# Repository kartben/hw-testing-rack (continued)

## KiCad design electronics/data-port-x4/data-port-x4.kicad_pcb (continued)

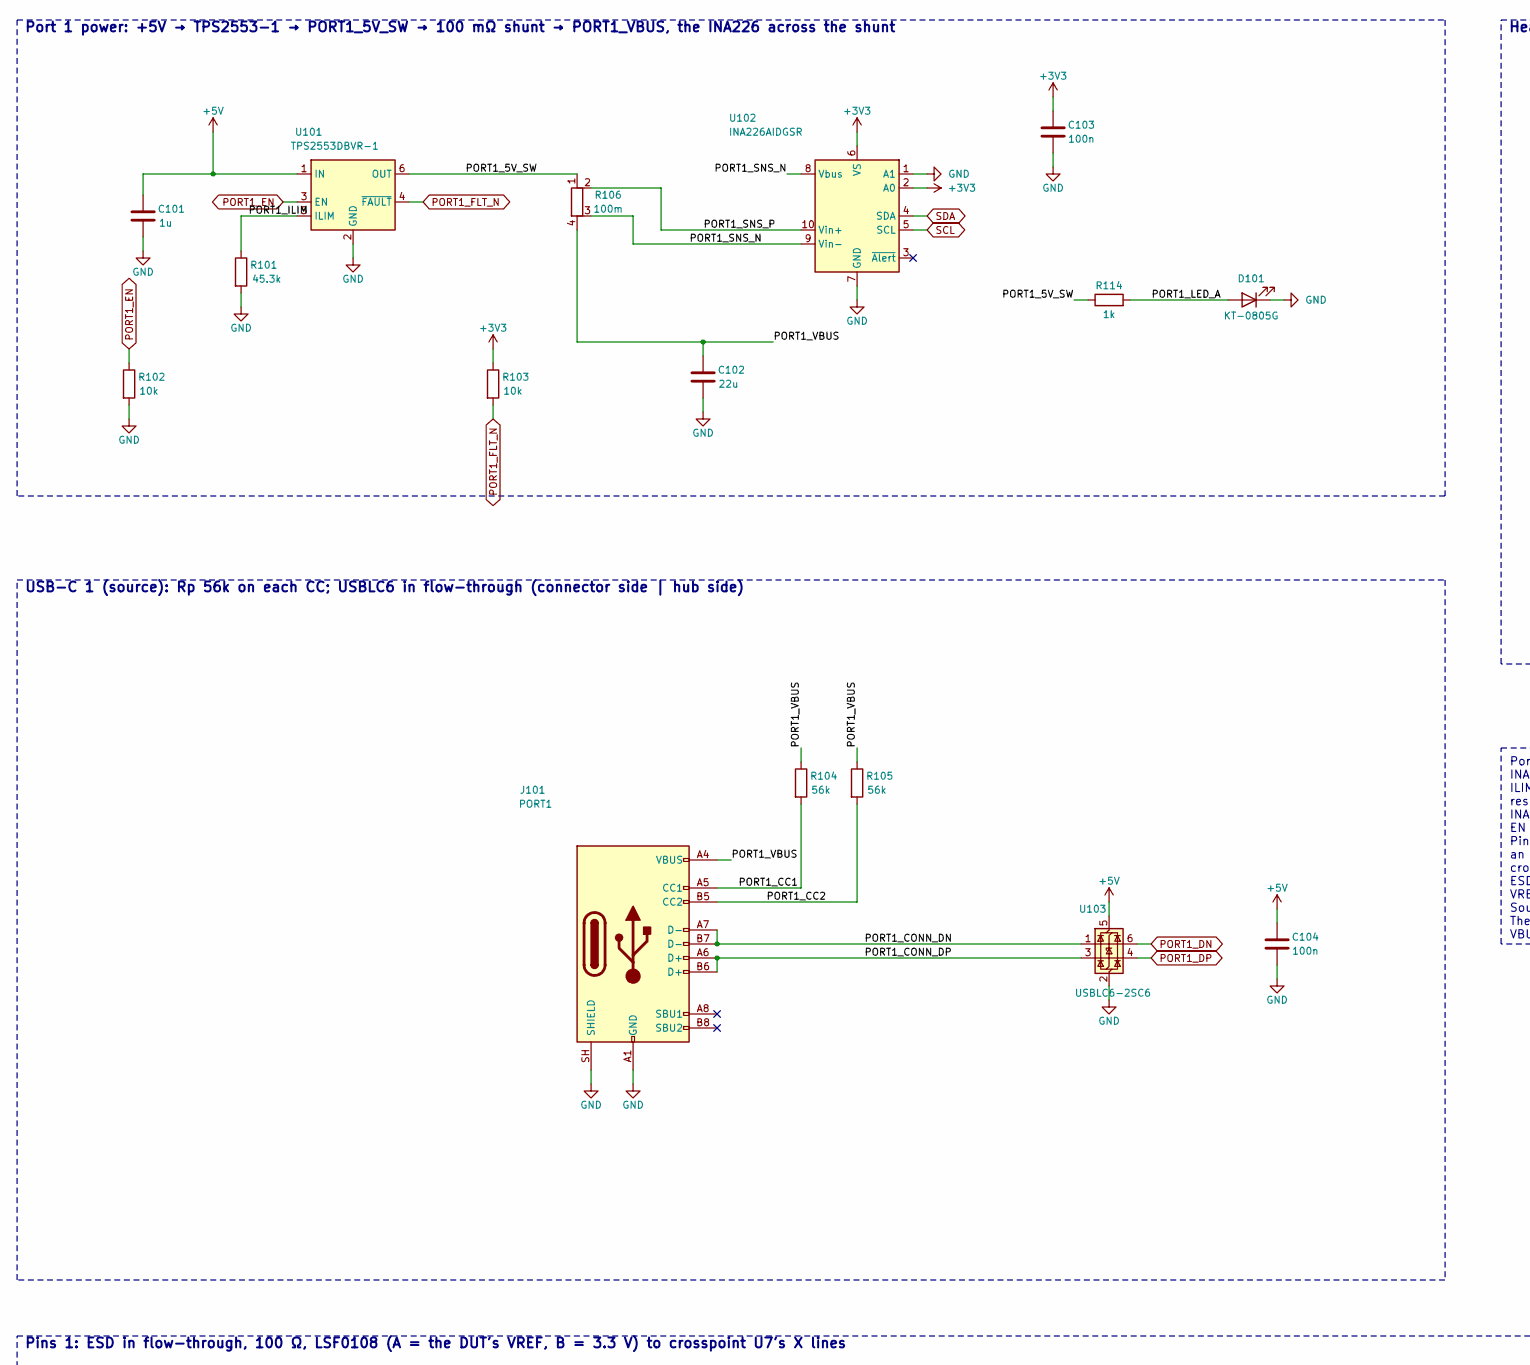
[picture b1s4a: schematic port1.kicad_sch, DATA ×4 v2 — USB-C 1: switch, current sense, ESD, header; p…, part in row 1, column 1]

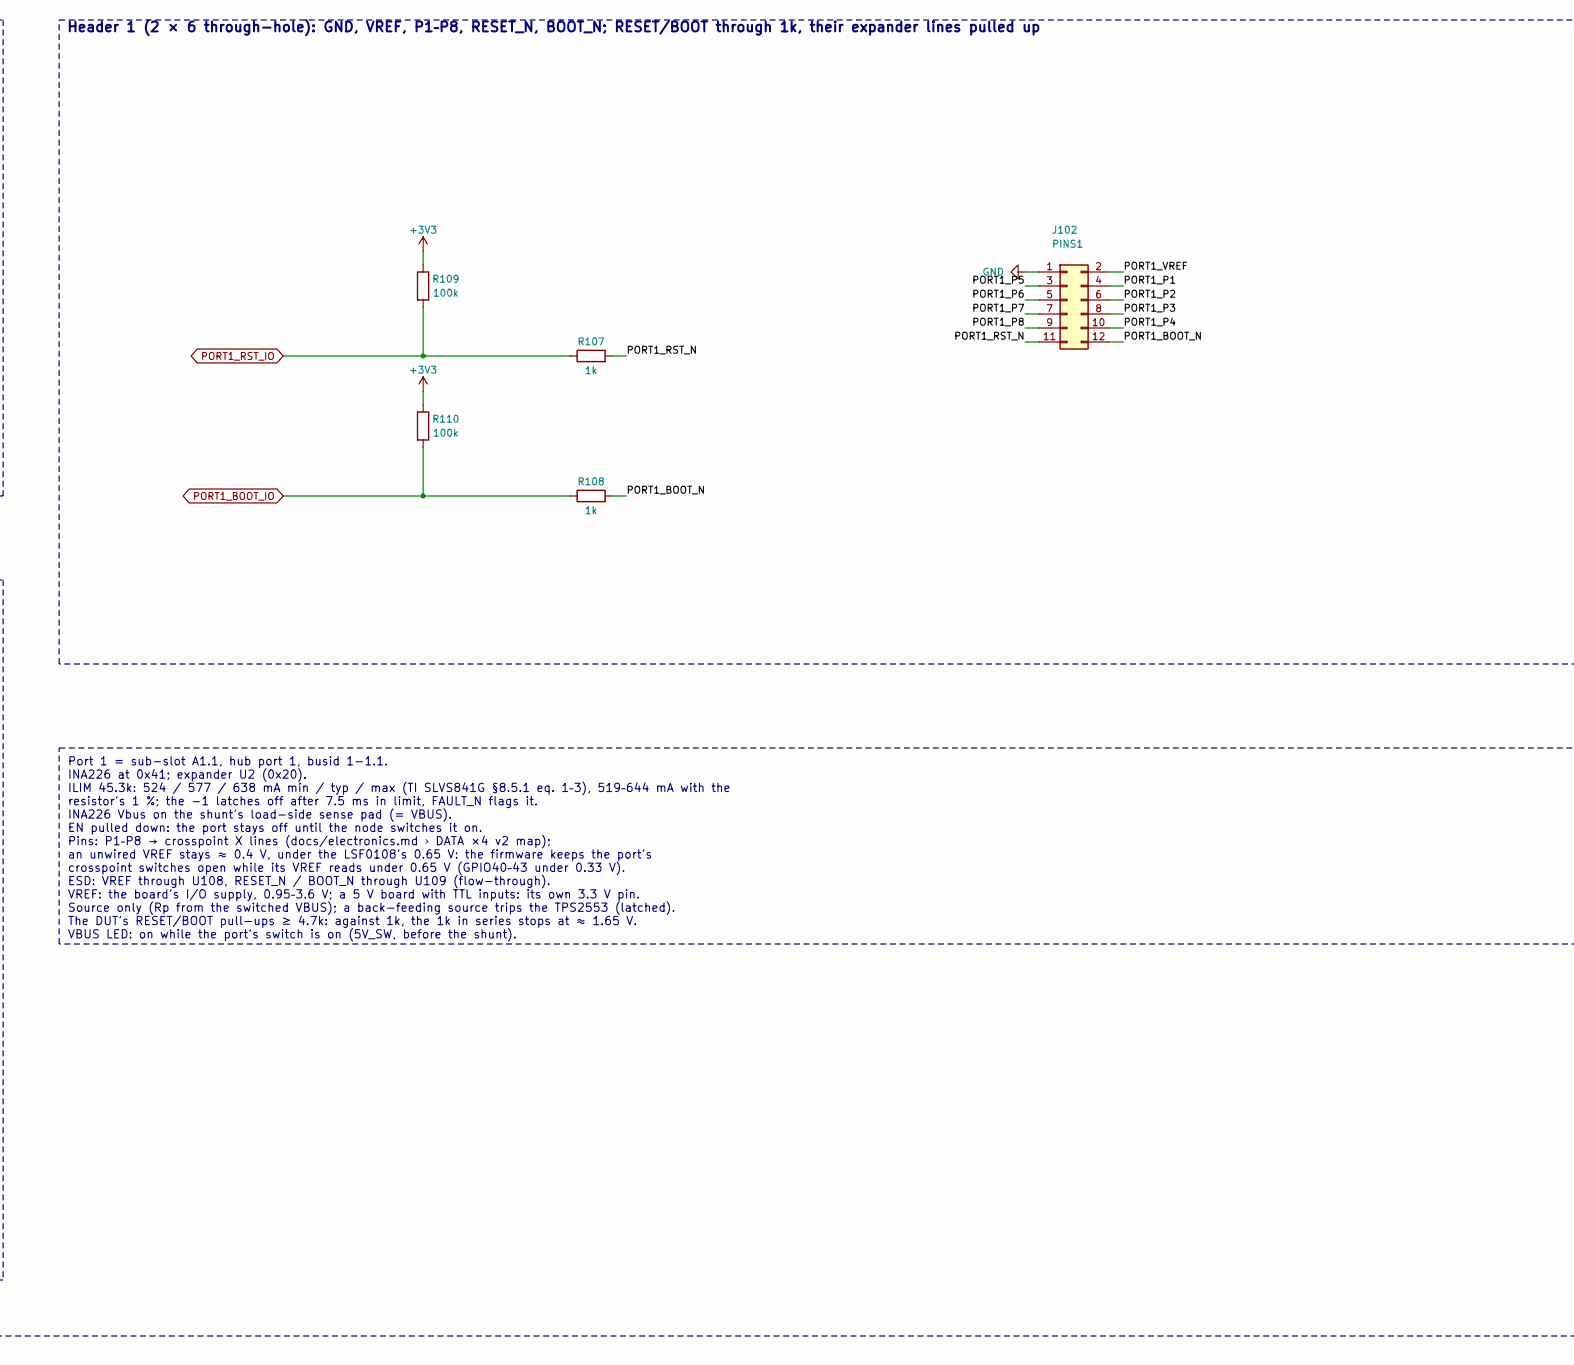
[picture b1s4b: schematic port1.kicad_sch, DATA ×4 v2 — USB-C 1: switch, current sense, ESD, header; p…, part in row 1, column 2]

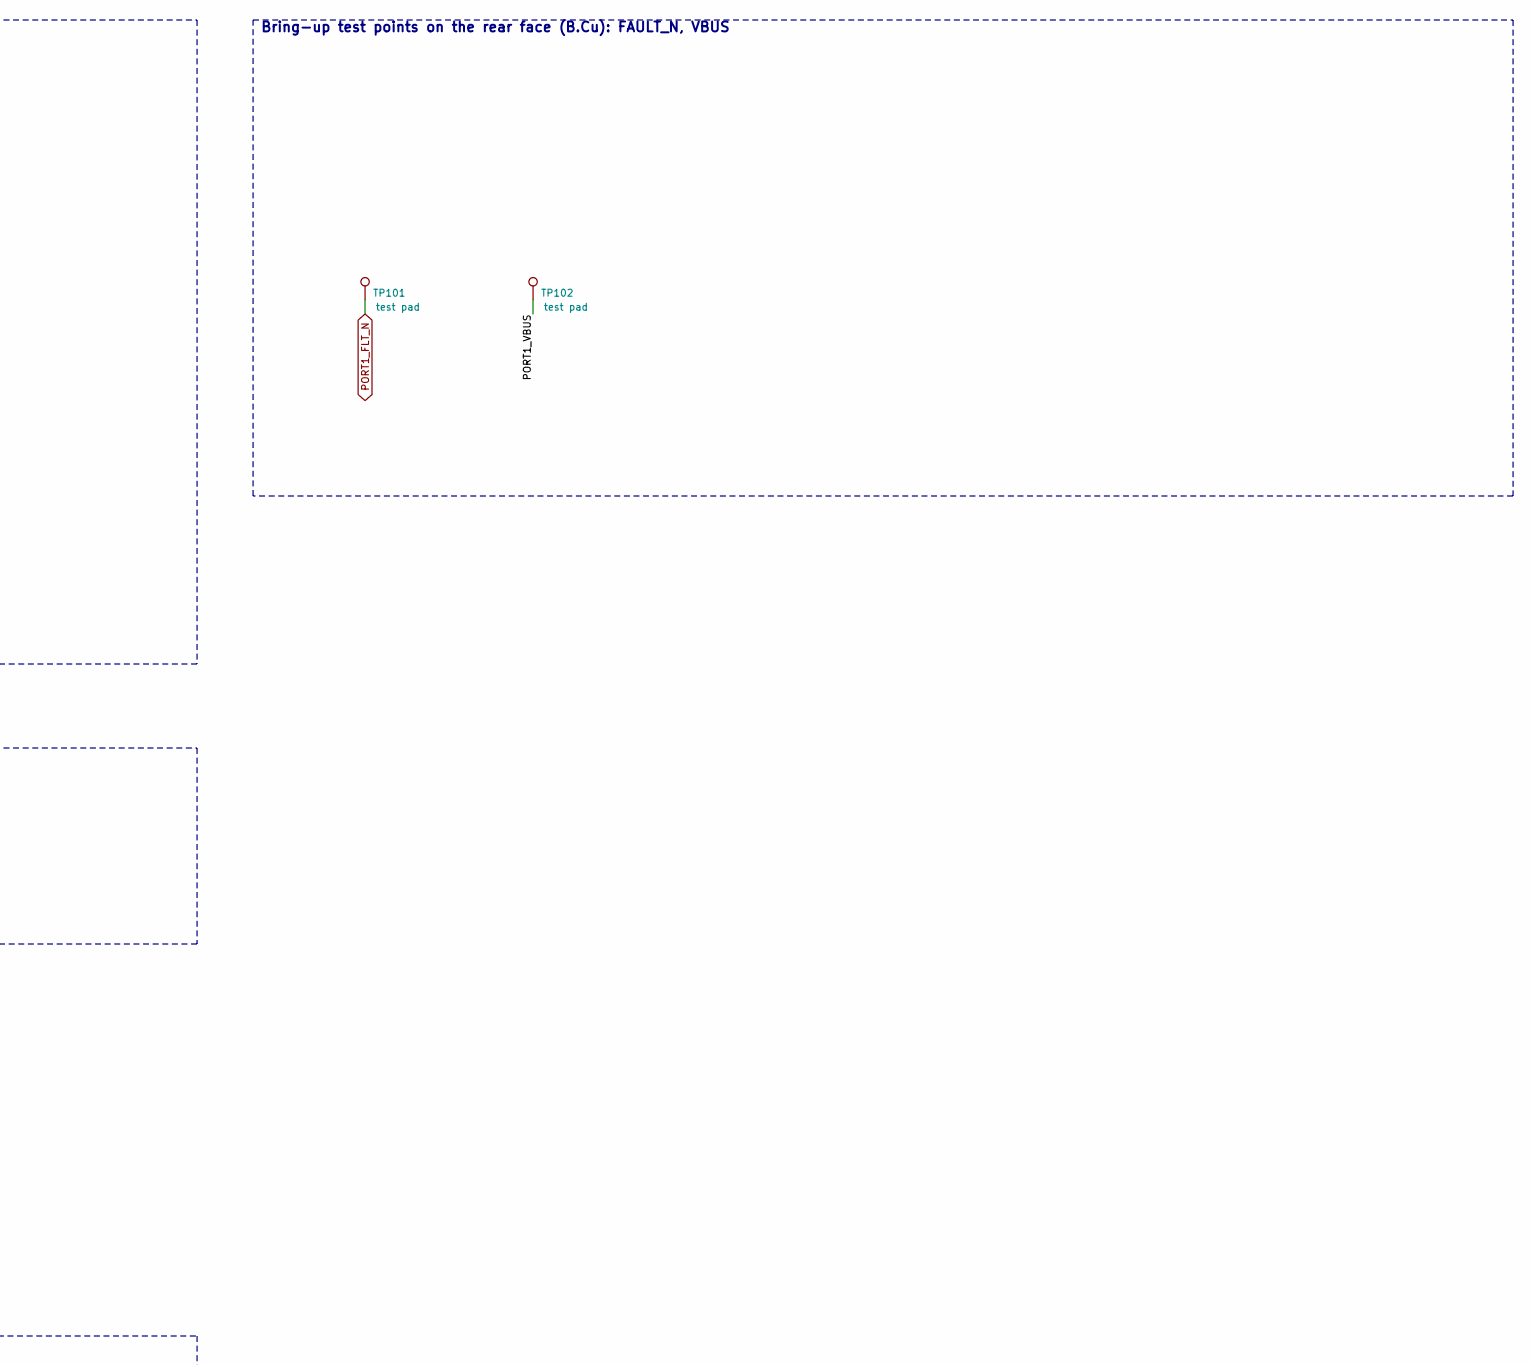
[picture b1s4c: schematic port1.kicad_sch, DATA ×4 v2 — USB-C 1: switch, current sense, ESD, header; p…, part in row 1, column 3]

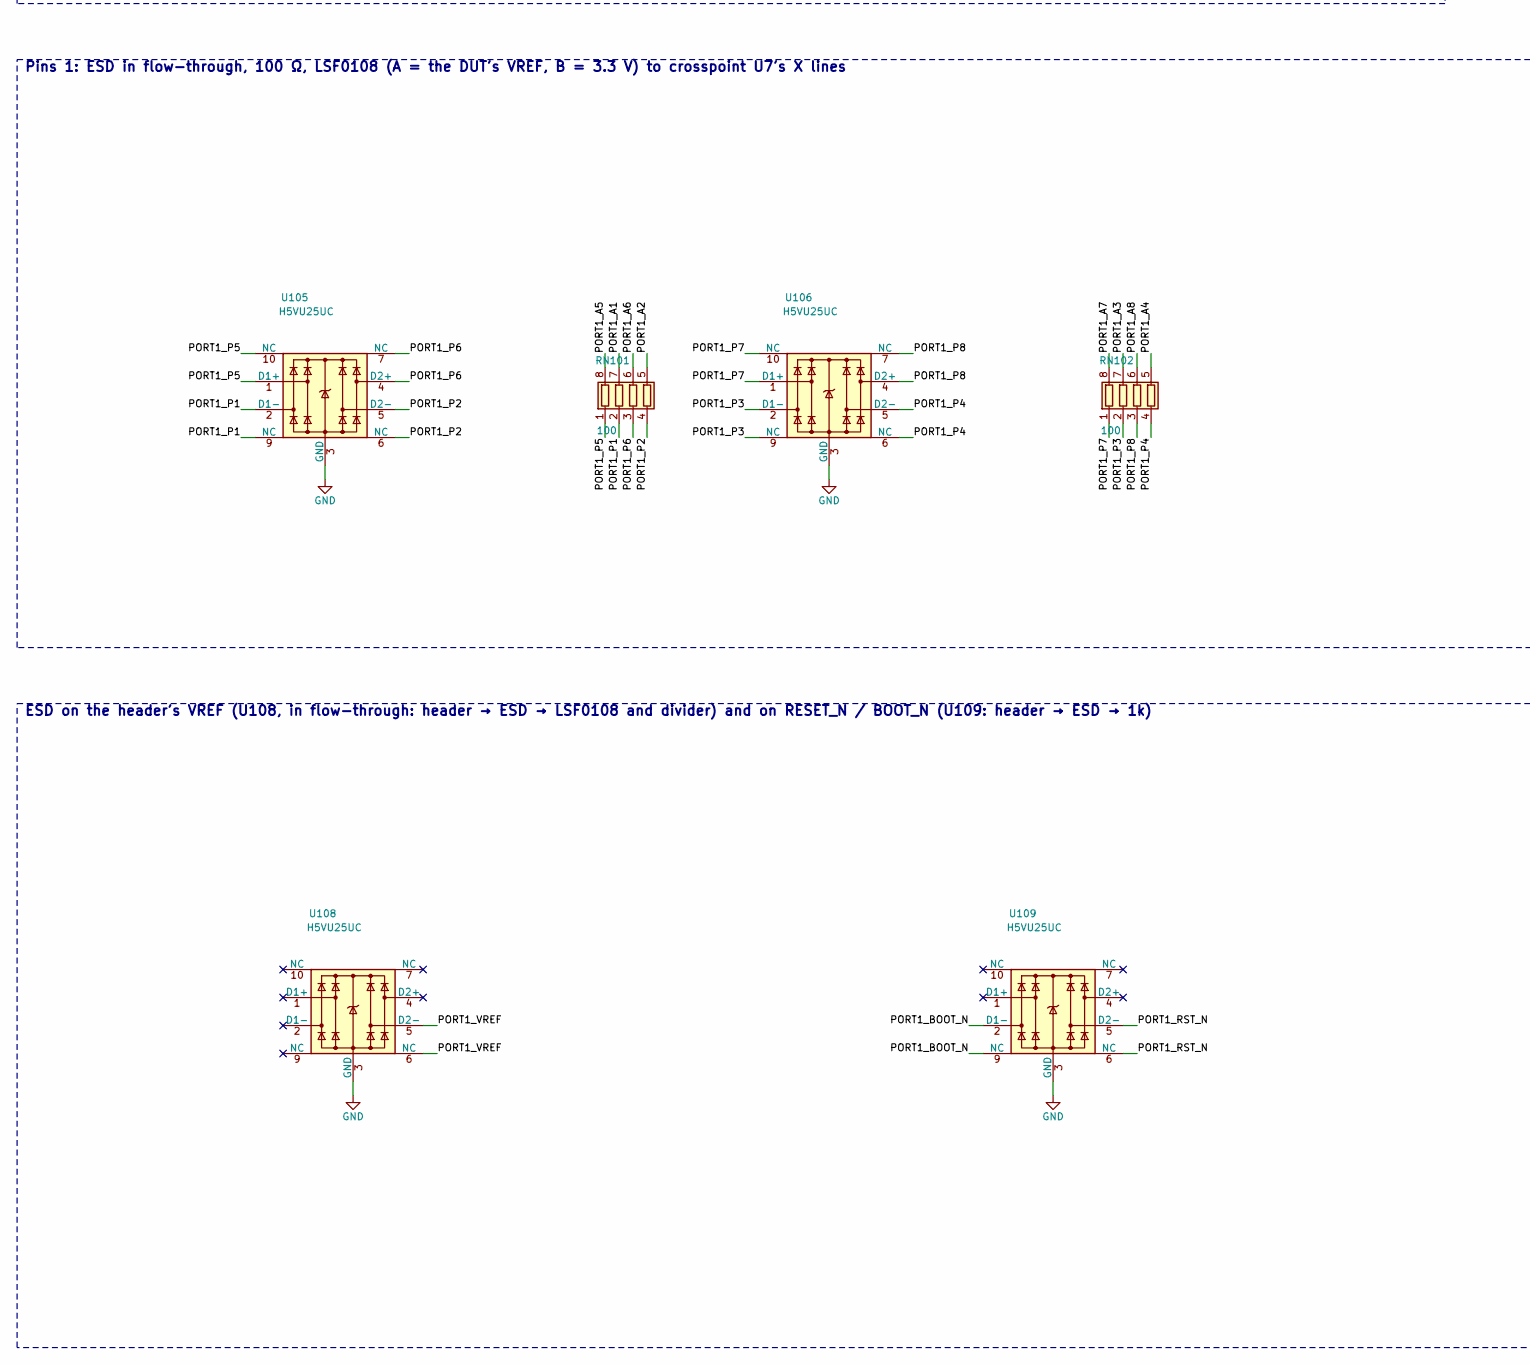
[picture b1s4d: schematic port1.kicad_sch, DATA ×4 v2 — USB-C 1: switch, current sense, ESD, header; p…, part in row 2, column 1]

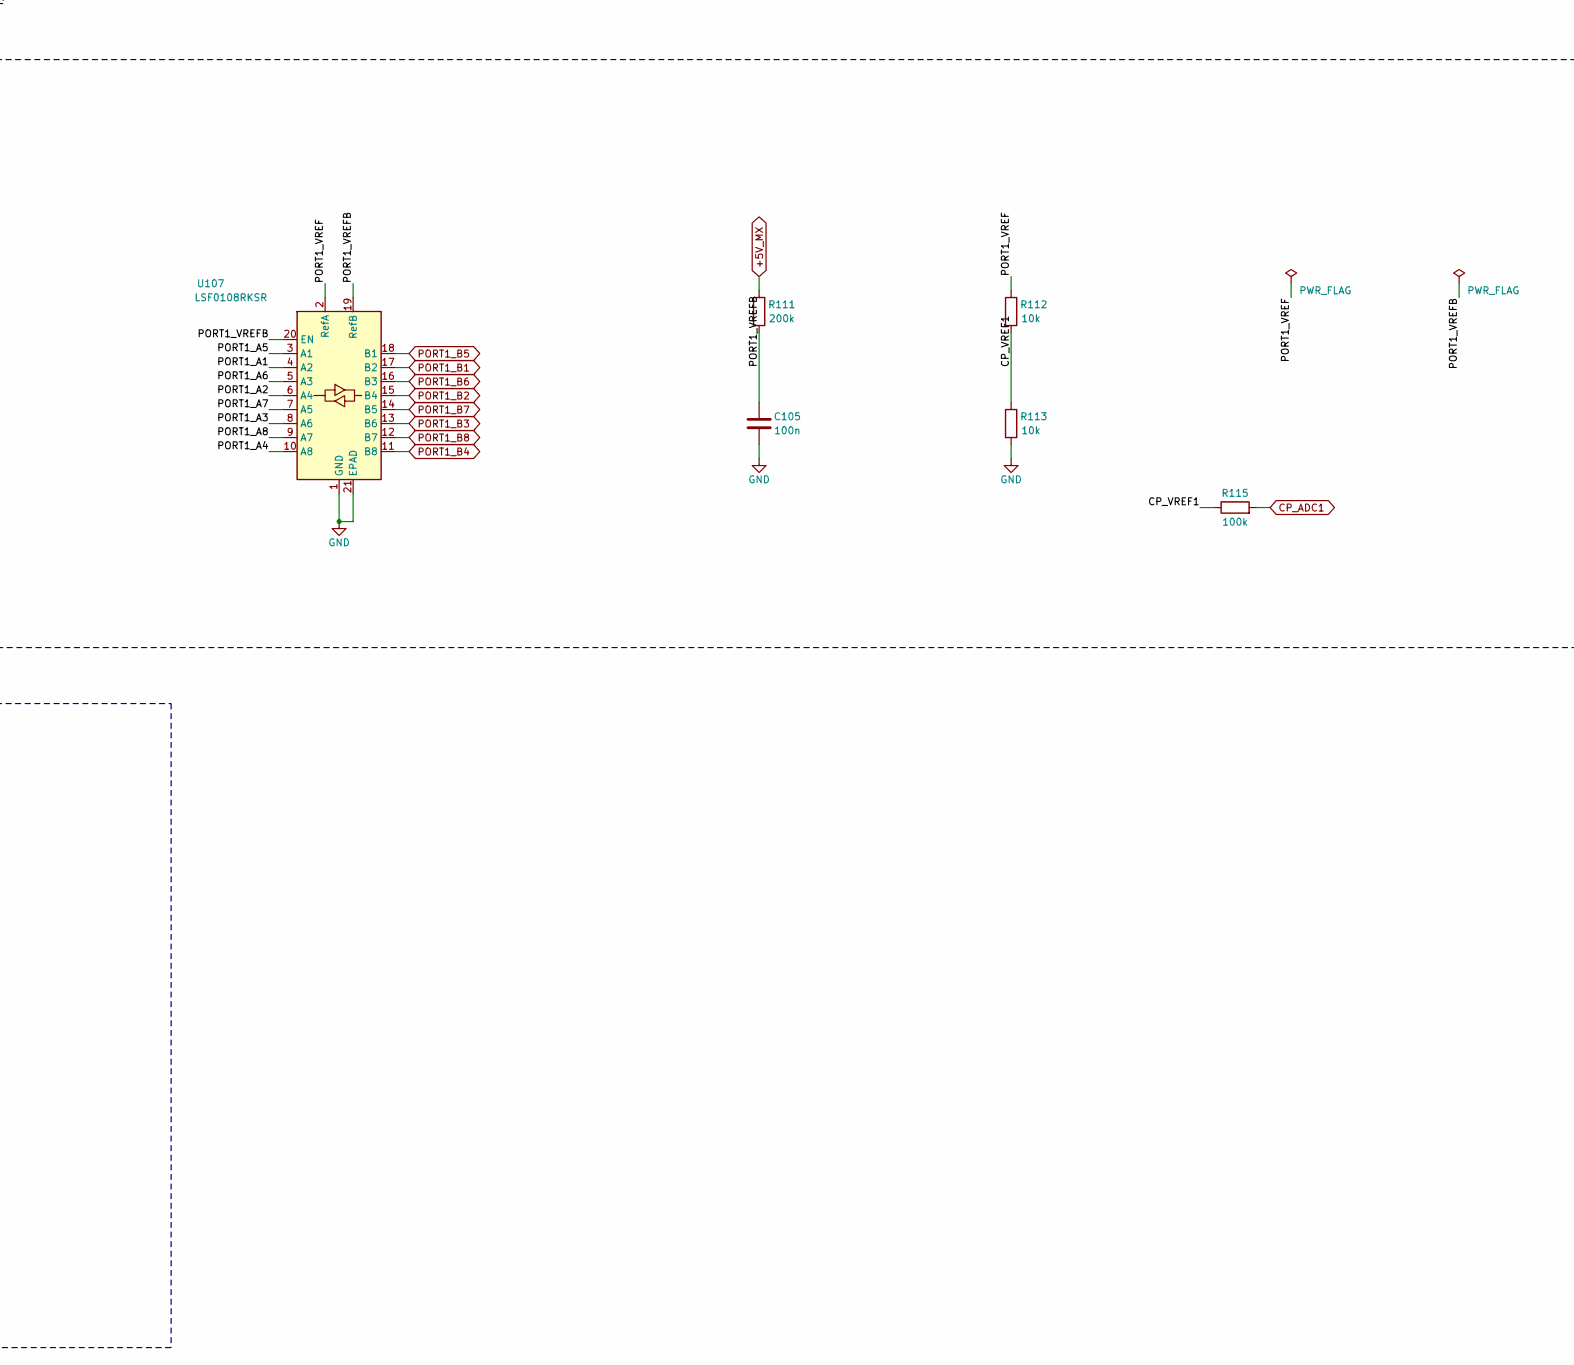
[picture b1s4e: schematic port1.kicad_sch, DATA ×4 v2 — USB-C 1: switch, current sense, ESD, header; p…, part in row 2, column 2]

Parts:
C101: 1u; C_0402_1005Metric; MPN CL05A105KA5NQNC; LCSC C52923
C102: 22u; C_0805_2012Metric; MPN CL21A226MAQNNNE; LCSC C45783
C103, C104, C105: 100n; C_0402_1005Metric; MPN CL05B104KO5NNNC; LCSC C1525
D101: KT-0805G; LED_0805_2012Metric; MPN KT-0805G; LCSC C2297
J101: PORT1; USB_C_Receptacle_GCT_USB4145-03-0170-C_Vertical; MPN USB4145-03-0170-C; LCSC C5181332
J102: PINS1; PinHeader_2x06_P2.54mm_Vertical; MPN HX PZ2.54-2x6P ZZ; LCSC C32713279
R101: 45.3k; R_0402_1005Metric; MPN FRC0402F4532TS; LCSC C2933099
R102, R103, R112, R113: 10k; R_0402_1005Metric; MPN 0402WGF1002TCE; LCSC C25744
R104, R105: 56k; R_0402_1005Metric; MPN 0402WGF5602TCE; LCSC C25796
R106: 100m; R_1206_3216Metric_Kelvin; MPN 1206W4F100LT5E; LCSC C25334
R107, R108, R114: 1k; R_0402_1005Metric; MPN 0402WGF1001TCE; LCSC C11702
R109, R110, R115: 100k; R_0402_1005Metric; MPN 0402WGF1003TCE; LCSC C25741
R111: 200k; R_0402_1005Metric; MPN 0402WGF2003TCE; LCSC C25764
RN101, RN102: 100; R_Array_Convex_4x0402; MPN 4D02WGJ0101TCE; LCSC C48442
TP101: test pad; TestPoint_Pad_D1.0mm; MPN test pad
TP102: test pad; TestPoint_Pad_D1.5mm; MPN test pad
U101: TPS2553DBVR-1; SOT-23-6; MPN TPS2553DBVR-1; LCSC C111738
U102: INA226AIDGSR; TSSOP-10_3x3mm_P0.5mm; MPN INA226AIDGSR; LCSC C49851
U103: USBLC6-2SC6; SOT-23-6; MPN USBLC6-2SC6; LCSC C7519
U105, U106, U108, U109: H5VU25UC; DFN2510-10L_2.5x1.0mm_P0.5mm; MPN H5VU25UC; LCSC C20615800
U107: LSF0108RKSR; DHVQFN-20-1EP_2.5x4.5mm_P0.5mm_EP1x3mm; MPN LSF0108RKSR; LCSC C130008

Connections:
+3V3: C103.1, R103.1, R109.1, R110.1, U102.2 (A0), U102.6 (VS); also elsewhere on the board
+5V: C101.1, C104.1, U101.1 (IN), U103.5 (VBUS); also elsewhere on the board
+5V_MX: R111.1; also elsewhere on the board
/Port 1/CP_VREF1: R112.2, R113.1, R115.1
/Port 1/PORT1_5V_SW: R106.1, R114.1, U101.6 (OUT)
/Port 1/PORT1_A1: RN101.7 (R2.2), U107.4 (A2)
/Port 1/PORT1_A2: RN101.5 (R4.2), U107.6 (A4)
/Port 1/PORT1_A3: RN102.7 (R2.2), U107.8 (A6)
/Port 1/PORT1_A4: RN102.5 (R4.2), U107.10 (A8)
/Port 1/PORT1_A5: RN101.8 (R1.2), U107.3 (A1)
/Port 1/PORT1_A6: RN101.6 (R3.2), U107.5 (A3)
/Port 1/PORT1_A7: RN102.8 (R1.2), U107.7 (A5)
/Port 1/PORT1_A8: RN102.6 (R3.2), U107.9 (A7)
/Port 1/PORT1_BOOT_N: J102.12, R108.2, U109.2 (D1-), U109.9 (NC)
/Port 1/PORT1_CC1: J101.A5 (CC1), R104.2
/Port 1/PORT1_CC2: J101.B5 (CC2), R105.2
/Port 1/PORT1_CONN_DN: J101.A7 (D-), J101.B7 (D-), U103.1 (I/O1)
/Port 1/PORT1_CONN_DP: J101.A6 (D+), J101.B6 (D+), U103.3 (I/O2)
/Port 1/PORT1_ILIM: R101.1, U101.5 (ILIM)
/Port 1/PORT1_LED_A: D101.2 (A), R114.2
/Port 1/PORT1_P1: J102.4, RN101.2 (R2.1), U105.2 (D1-), U105.9 (NC)
/Port 1/PORT1_P2: J102.6, RN101.4 (R4.1), U105.5 (D2-), U105.6 (NC)
/Port 1/PORT1_P3: J102.8, RN102.2 (R2.1), U106.2 (D1-), U106.9 (NC)
/Port 1/PORT1_P4: J102.10, RN102.4 (R4.1), U106.5 (D2-), U106.6 (NC)
/Port 1/PORT1_P5: J102.3, RN101.1 (R1.1), U105.1 (D1+), U105.10 (NC)
/Port 1/PORT1_P6: J102.5, RN101.3 (R3.1), U105.4 (D2+), U105.7 (NC)
/Port 1/PORT1_P7: J102.7, RN102.1 (R1.1), U106.1 (D1+), U106.10 (NC)
/Port 1/PORT1_P8: J102.9, RN102.3 (R3.1), U106.4 (D2+), U106.7 (NC)
/Port 1/PORT1_RST_N: J102.11, R107.2, U109.5 (D2-), U109.6 (NC)
/Port 1/PORT1_SNS_N: R106.3, U102.8 (Vbus), U102.9 (Vin-)
/Port 1/PORT1_SNS_P: R106.2, U102.10 (Vin+)
/Port 1/PORT1_VBUS: C102.1, J101.A4 (VBUS), J101.A9 (VBUS), J101.B4 (VBUS), J101.B9 (VBUS), R104.1, R105.1, R106.4, TP102.1
/Port 1/PORT1_VREF: J102.2, R112.1, U107.2 (RefA), U108.5 (D2-), U108.6 (NC)
/Port 1/PORT1_VREFB: C105.1, R111.2, U107.19 (RefB), U107.20 (EN)
CP_ADC1: R115.2; also elsewhere on the board
GND: C101.2, C102.2, C103.2, C104.2, C105.2, D101.1 (K), J101.A1 (GND), J101.A12 (GND), J101.B1 (GND), J101.B12 (GND), J101.SH (SHIELD), J102.1, R101.2, R102.2, R113.2, U101.2 (GND), U102.1 (A1), U102.7 (GND), U103.2 (GND), U105.3 (GND), U105.8 (GND), U106.3 (GND), U106.8 (GND), U107.1 (GND), U107.21 (EPAD), U108.3 (GND), U108.8 (GND), U109.3 (GND), U109.8 (GND); also elsewhere on the board
PORT1_B1: U107.17 (B2); also elsewhere on the board
PORT1_B2: U107.15 (B4); also elsewhere on the board
PORT1_B3: U107.13 (B6); also elsewhere on the board
PORT1_B4: U107.11 (B8); also elsewhere on the board
PORT1_B5: U107.18 (B1); also elsewhere on the board
PORT1_B6: U107.16 (B3); also elsewhere on the board
PORT1_B7: U107.14 (B5); also elsewhere on the board
PORT1_B8: U107.12 (B7); also elsewhere on the board
PORT1_BOOT_IO: R108.1, R110.2; also elsewhere on the board
PORT1_DN: U103.6 (I/O1); also elsewhere on the board
PORT1_DP: U103.4 (I/O2); also elsewhere on the board
PORT1_EN: R102.1, U101.3 (EN); also elsewhere on the board
PORT1_FLT_N: R103.2, TP101.1, U101.4 (~FAULT); also elsewhere on the board
PORT1_RST_IO: R107.1, R109.2; also elsewhere on the board
SCL: U102.5 (SCL); also elsewhere on the board
SDA: U102.4 (SDA); also elsewhere on the board

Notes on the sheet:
Port 1 power: +5V → TPS2553-1 → PORT1_5V_SW → 100 mΩ shunt → PORT1_VBUS, the INA226 across the shunt
Bring-up test points on the rear face (B.Cu): FAULT_N, VBUS
USB-C 1 (source): Rp 56k on each CC; USBLC6 in flow-through (connector side | hub side)
Header 1 (2 × 6 through-hole): GND, VREF, P1–P8, RESET_N, BOOT_N; RESET/BOOT through 1k, their expander lines pulled up
ESD on the header's VREF (U108, in flow-through: header → ESD → LSF0108 and divider) and on RESET_N / BOOT_N (U109: header → ESD → 1k)
Pins 1: ESD in flow-through, 100 Ω, LSF0108 (A = the DUT's VREF, B = 3.3 V) to crosspoint U7's X lines
Port 1 = sub-slot A1.1, hub port 1, busid 1-1.1. INA226 at 0x41; expander U2 (0x20). ILIM 45.3k: 524 / 577 / 638 mA min / typ / max (TI SLVS841G §8.5.1 eq. 1–3), 519–644 mA with the resistor's 1 %; the -1 latches off after 7.5 ms in limit, FAULT_N flags it. INA226 Vbus on the shunt's load-side sens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
